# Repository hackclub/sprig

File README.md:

# 🍃 Hack Club Sprig 🍃🍃🍃

**[💻 Online Editor: Make a game](https://sprig.hackclub.com/editor)** | **[👀 Gallery: Find games](https://sprig.hackclub.com/gallery)** | **[🕸 Landing Page](https://sprig.hackclub.com)** | **[🎮 Firmware](https://github.com/hackclub/sprig/tree/main/firmware/spade)** | **[👾 Engine](https://github.com/hackclub/sprig-engine)**

[Sprig](https://sprig.hackclub.com) is a game console where **every user is a creator**. It can only be obtained by building a tile-based game in the [web-based game editor](https://sprig.hackclub.com/editor) and shipping it in the [community gallery](https://sprig.hackclub.com/gallery). It's made by [Hack Club](https://hackclub.com).

<p align="left">

</p>

You should be able to get started in Sprig with very little programming experience. Even if you're an expert, you should still be able to have fun. Sprig games are designed to be shared and hacked on with friends. Every game submitted is easily viewable and editable in our gallery allowing people to learn from and build off each other. 

## Sprig is a...

...**custom handheld game console** built by Hack Club. we are giving a Sprig to every teenage hacker that successfully shares a game they create in our [community gallery](https://sprig.hackclub.com/gallery).

<p align="left">

</p>

...**[web-based game editor](https://sprig.hackclub.com/editor)** that transforms learning to code from studying language syntax to making small creative projects. The Sprig game engine exposes a small construction kit for making tile-based games. This construction kit helps you focus on being creative instead of learning big APIs. The games are just JavaScript and we built a custom system to run that same JavaScript on the microcontroller!

<p align="left">

</p>

...**[hardware development kit](https://github.com/hackclub/sprig/blob/main/docs/ASSEMBLY.md)**. It's not just for gaming! The Sprig console is designed to be assembled and disassembled. Each kit includes parts needed for getting started with hardware engineering and embedded systems programming. This includes a Raspberry Pi Pico, a TFT7735 screen, a MAX98357A I2S class D audio amplifier, a whole bunch of buttons, LEDs, a speaker, and a carrier board which wires all these components together while exposing the remaining pins on the microcontroller. It's a complete system for generating graphics, sound, and handling tactile inputs which is reprogrammable at the touch of a button.

<p align="left">

</p>

## Fully open source

**Sprig is open source**. Shipping a game to the Sprig Gallery is contributing to an open-source project. Everything about Sprig is transparent and editable. That includes the [hardware designs](https://github.com/hackclub/sprig/tree/main/hardware), the [game engine](https://github.com/hackclub/sprig/tree/main/engine), the [embedded game engine for the RP2040 chip](https://github.com/hackclub/sprig/tree/main/firmware/spade), and the editor and website itself in this repo!

We did some fun engineering to get Sprig to work and to make your games run the same on your desktop computer and a $4 microcontroller. That involved custom JS runtimes with optimizations in C and even PIO assembly. We also documented some [behind-the-scenes](https://github.com/hackclub/sprig/tree/main/docs).

## You Ship, We Ship

Make a game
&rarr; Share it with the community
&rarr; Receive your device
&rarr; Play Sprig games on it
&rarr; Hack on the device for more projects

***Only teenagers and younger can receive Sprigs!*** All are welcome to submit to the [gallery](https://sprig.hackclub.com/gallery) though.

## Philosophy

People learn best when they make things that they care about, which they can then share with others. This type of learning philosophy is called constructionism, and Sprig is a type of microworld. A microworld is an environment where you can discover programming by using it to express yourself. 

## Tutorials

To get started you can follow [this challenge in the editor](https://sprig.hackclub.com/gallery/getting_started), check out some [Sprig workshops](https://workshops.hackclub.com#sprig) or [Sprig jams](https://jams.hackclub.com/batch/sprig).

## Development

Join the `#sprig` channel on the [Hack Club Slack](https://hackclub.com/slack/) where you can join the development discussion and ask for help. We also have other channels for Sprig specific stuff:

- `#sprig-platform`: For discussion of development of the Sprig platform as a whole. 
- `#sprig-gaming-controller`: Building a case for the Sprig console to make it a portable gaming controller.
- `#sprig-emulator`: Development of a Gameboy emulator for Sprig.
- `#sprig-multiplayer`: Development of multiplayer support.
- `#sprig-lora`: Development of Sprig-Lora communicator.
- `#sdsprig`: Development of Sprig loading from an SD Card.
- `#sprig-minecraft`: Development of Minecraft for Sprig.
- `#sprig-ios-app`: Development of iOS app.
- `#sprig-engagement`: Development of a bot to post every new game to `#sprig`.
- `#vs-sprig`: Development of Sprig extension for VS Code.
- `#stationary-sprig`: Making Sprig a home console.
- `#spriggy-doom`: Development of a clone of Doom.
- `#sprigos-development`: Development of the sprigOS, the sprig game that acts like an operating system.
- `#spade`: For discussions of Spade firmware/OS of the Sprig.
- `#spaint`: Make art with your sprig with sPaint and share.

Learn more about how to make games with Sprig check out the [docs](https://github.com/hackclub/sprig/tree/main/docs).

### Tech Stack

Sprig's editor and site pages are built with [Astro](https://astro.build/) (SSR via `@astrojs/node`) using [Preact](https://preactjs.com/) for rendering. Perhaps somewhat unusually, we predominantly use [Preact Signals](https://preactjs.com/guide/v10/signals/) for state management. The code editor uses [CodeMirror](https://codemirror.net/). There is one legacy [Svelte](https://svelte.dev/) component on the homepage. The database is [Firebase](https://firebase.google.com/). Everything pushed to GitHub and all pull requests are automatically deployed on [Vercel](https://vercel.com/hackclub).

### Repo Structure

```tree
sprig/
├── src/                        # Astro website + editor
│   ├── pages/                  # Pages (.astro) and API routes (.ts), all SSR
│   ├── components/             # Preact (TSX) UI components + CSS modules
│   ├── lib/                    # Shared support code (server + client)
│   ├── legacy/                 # Old Svelte code kept for the homepage
│   ├── layouts/                # Astro layout templates
│   ├── integrations/           # Custom Astro integrations
│   ├── translations/           # i18n strings
│   ├── global.css              # Global styles
│   └── middleware.ts           # Astro middleware
│
├── engine/                     # Sprig game engine (separate package)
├── games/                      # Community-submitted game files (.js)
├── public/                     # Static assets (game metadata, images, fonts)
├── firmware/                   # RP2040 embedded firmware (Spade runtime + HAL)
├── hardware/                   # PCB designs + 3D-printable console cases
├── docs/                       # Documentation (assembly, getting started, runbooks)
├── scripts/                    # Python admin tools (plagiarism check, review, etc.)
├── bin/                        # lint-sprig game linter
├── tests/                      # Fuzzy tests for the engine
├── yjs-client/                 # Yjs WebRTC client for collaborative editing
├── yjs-signaling-server/       # Yjs signaling server (separate deploy)
├── font-things/                # Font manipulation script
└── sprig-hax/                  # Community hardware mods (gyro, etc.)
```

Key source directories explained:

- `src/pages/` contains all the site's main pages and API routes. In general, `.ts` files are API routes and `.astro` files are pages. All pages are server-side rendered on demand and can make database calls and such.
- `src/components/` contains all the components used in the editor and site pages. Most components will have accompanying `.module.css` files which contain vanilla CSS stylesheets which are scoped to the component. These "CSS modules" can be imported as a JS object containing referencable class names.
- `src/lib/` contains all the support code. Currently this is a mix of server and client code.
- `src/legacy/` has a bunch of old code from the v1 version of the editor which is kept for ease of porting the home and Get a Sprig pages. Since Astro lets us combine multiple frameworks, we're also using old Svelte code in some places.
- `docs/` contains documentation on how to use Sprig, including `docs.md` which contains the help file embedded in the editor.
- `public/` contains static assets which are directly served.
- `src/global.css` and `src/components/standard-head.astro` contain code that's generally shared across all pages.

### Prerequisites

Things you'll want installed:

- [Git](https://git-scm.com/)
- [Bun](https://bun.sh/)

We use Firebase as a database. To develop login/saving related features locally, you'll likely want to [create a Firebase project](https://console.firebase.google.com/) for yourself. Then, create a service account, download the JSON file, and convert the contents to base64 ([link to a tool to easily do this](https://gchq.github.io/CyberChef/#recipe=JSON_Minify()To_Base64('A-Za-z0-9%2B/%3D'))).

We recommend [Visual Studio Code](https://code.visualstudio.com/) as a code editor. You should be automatically prompted to install some recommended extensions when you open the project.

### Project Setup

In a terminal, clone the repo and install packages:

```bash
git clone https://github.com/hackclub/sprig/
cd sprig
bun install
```

Next, you'll want to give Sprig access to the Firebase credentials, as well as some extra credentials that you can request from the @creds team on Slack. Complete the `.env.example` file with those credentials and rename it to `.env`.

To start the dev server, run `bun dev` and visit <http://localhost:4321> in your web browser! Please create a GitHub issue if you cannot get something to work properly.

### Running Tests

```bash
bun test          # fuzzy engine tests
bun run test:unit # vitest unit tests
```

### Docker

```bash
docker compose up
```

This starts the Astro site (port 9996), yjs-client, and yjs-signaling-server.

### Engine Development

All *engine code* (responsible for running games, playing tunes, etc.) is in a different repo: <https://github.com/hackclub/sprig-engine/>.

If you want to work on the engine and test out your changes in the context of this repo, you'll want to use a feature called linking.

First set up the engine repo:

```bash
git clone https://github.com/hackclub/sprig-engine/
cd sprig-engine
bun install
bun link
```

Then, in this website's repo:

```bash
bun link sprig
```

Now, run `bun dev` in the engine repo to start the TypeScript build process.

## Acknowledgements

The Sprig was developed by a team at Hack Club with assistance from Brian Silverman (who helped develop Scratch and the precursor to Lego Mindstorms), Vadim Gerasimov (engineer at Google who helped create Tetris when he was 15), and Quentin Bolsée (researcher at MIT and Vrije University Brussels), and dozens contributions from teenage open-source developers!

We're also grateful for amazing open-source projects that make this possible like [Kaluma](https://kalumajs.org/), [JerryScript](https://jerryscript.net/), [uhtml](https://github.com/WebReflection/uhtml), and [CodeMirror](https://codemirror.net/).

## Responsibilities

Please refer to [this document](./RESPONSIBILITIES.md) for a list of current team members who are accountable for maintaining certain aspects of the Sprig platform.

## License

The Hack Club Sprig is open source and licensed under the [MIT License](./LICENSE). Fork, remix, and make it your own! Pull requests and other contributions greatly appreciated.

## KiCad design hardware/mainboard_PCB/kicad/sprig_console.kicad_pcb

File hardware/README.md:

## The Sprig Console

You can find KiCAD 6 files for the PCB of Sprig, a BOM, and CAD models for the acrylic back covers here.

- `hardware/` contains the KiCAD files and Bill of Materials for the PCB
- `back_covers/` contains the CAD models for the acrylic back covers

The main [Sprig Repo is available here](https://www.github.com/hackclub/sprig).

# Description

The Sprig console is a custom-designed, limited edition game console powered by the Raspberry Pi Pico. It has a 1.8" 160x128 LCD display, as well as eight tactile buttons for input. It uses two AAA batteries for power, and has a MAX98357A audio amplifier with an 8 ohm, 300mW Speaker.

The Sprig console is a custom-designed, limited edition game console built to run games written with the Sprig game editor.

It's powered by a Raspberry Pi RP2040, which is clocked at 125MHz, with 264kB SRAM and 2MB external QSPI flash. Four unused GPIO pins are exposed to the rear of the console.

The Sprig is powered by two AAA batteries. There is also a high efficiency schottky diode to prevent power flow to the batteries when connected to USB power.

In addition, there is a MAX98357A class D audio amplifier from Maxim Integrated, connected to a CUI Devices CVS-1508 8 ohm, 300mW speaker.

There are two LEDs for status, a power switch for batteries, as well as eight tactile buttons to control input.

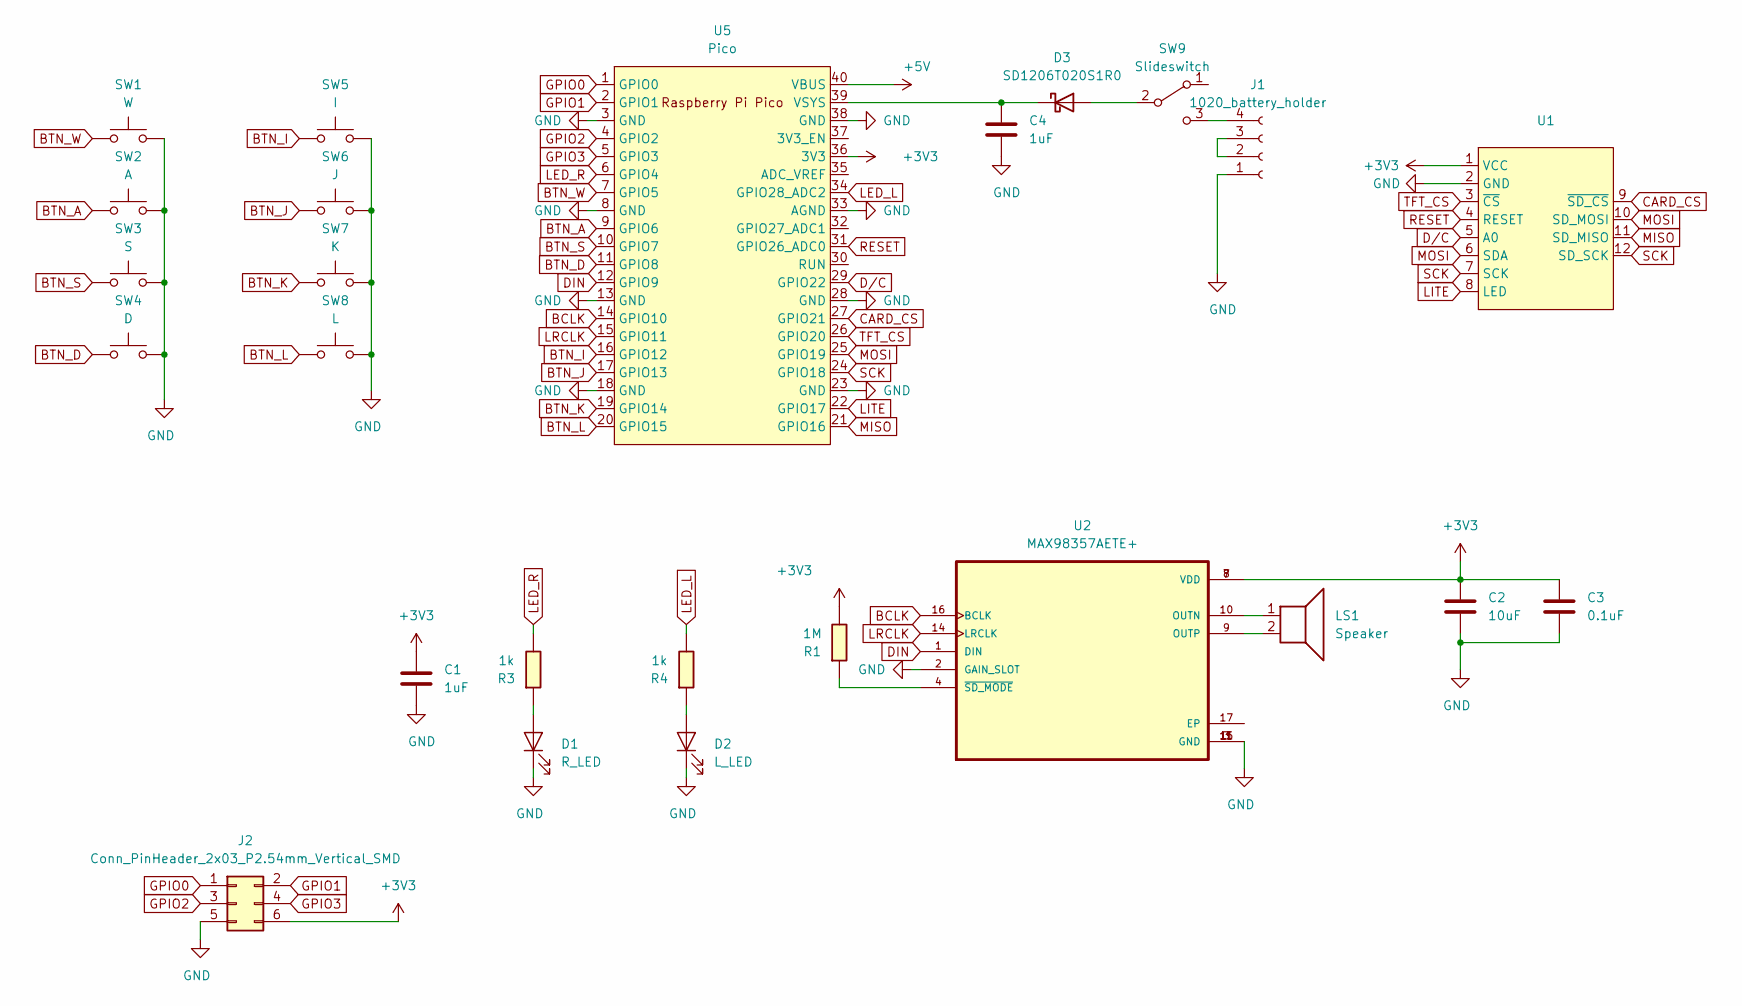
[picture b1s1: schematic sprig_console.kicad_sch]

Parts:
C1, C4: 1uF; C_1206
C2: 10uF; C_1206
C3: 0.1uF; C_1206
D1: R_LED; LED_1206
D2: L_LED; LED_1206
D3: SD1206T020S1R0; Diode_Schotky_100V_1A_Mini_SMA
J1: 1020_battery_holder; 1022
J2: Conn_PinHeader_2x03_P2.54mm_Vertical_SMD; PinHeader_2x03_P2.54mm_Vertical_SMD
LS1: Speaker; CVS-1508
R1: 1M; R_1206
R3, R4: 1k; R_1206
SW1: W; SW_PUSH-12mm_Wuerth-430476085716
SW2: A; SW_PUSH-12mm_Wuerth-430476085716
SW3: S; SW_PUSH-12mm_Wuerth-430476085716
SW4: D; SW_PUSH-12mm_Wuerth-430476085716
SW5: I; SW_PUSH-12mm_Wuerth-430476085716
SW6: J; SW_PUSH-12mm_Wuerth-430476085716
SW7: K; SW_PUSH-12mm_Wuerth-430476085716
SW8: L; SW_PUSH-12mm_Wuerth-430476085716
SW9: Slideswitch; slideswitchCK
U1: TFT_MSP1803
U2: MAX98357AETE+; QFN50P300X300X80-17N
U5: Pico; RPi_Pico_SMD_TH_mod

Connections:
+3V3: C1.1, C2.1, C3.1, J2.6, R1.1, U1.1 (VCC), U2.7 (VDD), U2.8 (VDD), U5.36 (3V3)
+5V: U5.40 (VBUS)
BCLK: U2.16 (BCLK), U5.14 (GPIO10)
BTN_A: SW2.1, U5.9 (GPIO6)
BTN_D: SW4.1, U5.11 (GPIO8)
BTN_I: SW5.1, U5.16 (GPIO12)
BTN_J: SW6.1, U5.17 (GPIO13)
BTN_K: SW7.1, U5.19 (GPIO14)
BTN_L: SW8.1, U5.20 (GPIO15)
BTN_S: SW3.1, U5.10 (GPIO7)
BTN_W: SW1.1, U5.7 (GPIO5)
CARD_CS: U1.9 (~SD_CS), U5.27 (GPIO21)
DIN: U2.1 (DIN), U5.12 (GPIO9)
D/C: U1.5 (A0), U5.29 (GPIO22)
GND: C1.2, C2.2, C3.2, C4.2, D1.1 (K), D2.1 (K), J1.1, J2.5, SW1.2, SW2.2, SW3.2, SW4.2, SW5.2, SW6.2, SW7.2, SW8.2, U1.2 (GND), U2.2 (GAIN_SLOT), U2.3 (GND), U2.11 (GND), U2.15 (GND), U5.3 (GND), U5.8 (GND), U5.13 (GND), U5.18 (GND), U5.23 (GND), U5.28 (GND), U5.33 (AGND), U5.38 (GND)
GPIO0: J2.1, U5.1 (GPIO0)
GPIO1: J2.2, U5.2 (GPIO1)
GPIO2: J2.3, U5.4 (GPIO2)
GPIO3: J2.4, U5.5 (GPIO3)
LED_L: R4.1, U5.34 (GPIO28_ADC2)
LED_R: R3.1, U5.6 (GPIO4)
LITE: U1.8 (LED), U5.22 (GPIO17)
LRCLK: U2.14 (LRCLK), U5.15 (GPIO11)
MISO: U1.11 (SD_MISO), U5.21 (GPIO16)
MOSI: U1.6 (SDA), U1.10 (SD_MOSI), U5.25 (GPIO19)
unnamed: D1.2 (A), R3.2
unnamed: D2.2 (A), R4.2
unnamed: D3.2 (A), SW9.2 (B)
unnamed: C4.1, D3.1 (K), U5.39 (VSYS)
unnamed: J1.2, J1.3
unnamed: J1.4, SW9.3 (C)
unnamed: LS1.1, U2.10 (OUTN)
unnamed: LS1.2, U2.9 (OUTP)
unnamed: R1.2, U2.4 (~SD_MODE)
RESET: U1.4 (RESET), U5.31 (GPIO26_ADC0)
SCK: U1.7 (SCK), U1.12 (SD_SCK), U5.24 (GPIO18)
TFT_CS: U1.3 (~CS), U5.26 (GPIO20)

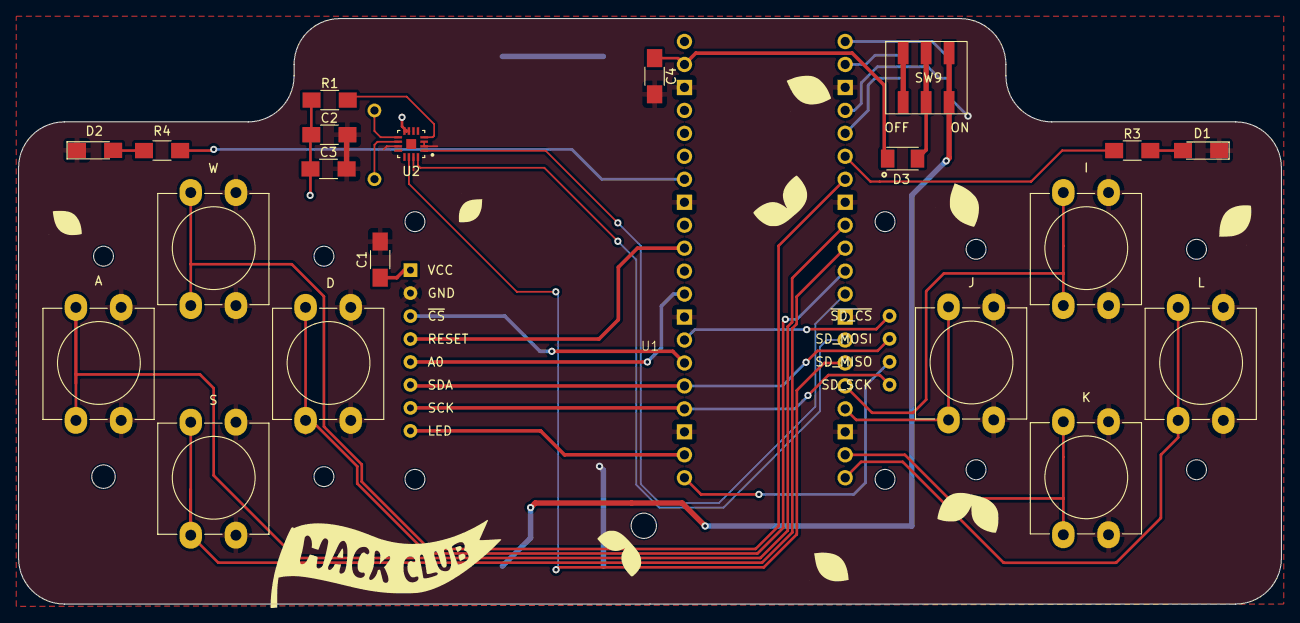
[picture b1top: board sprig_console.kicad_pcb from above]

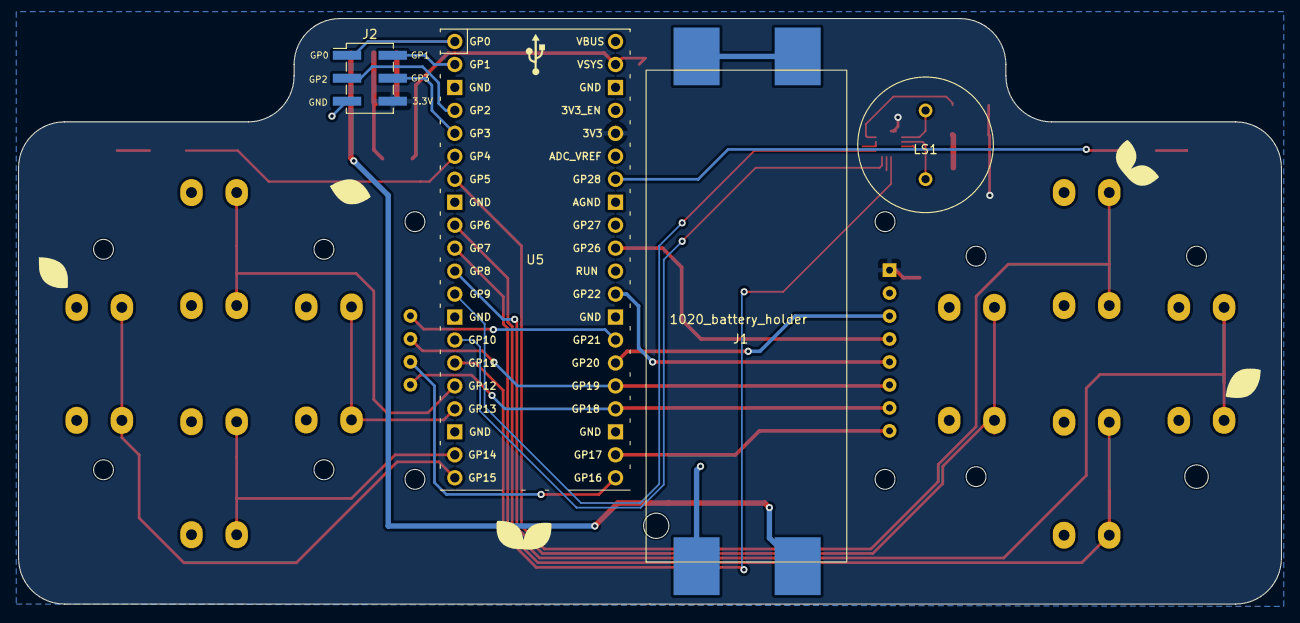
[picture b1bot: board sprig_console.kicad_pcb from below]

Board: 2 copper layers, 139.7 x 64.8 mm, 26 parts (5 on the bottom side), 36 nets.

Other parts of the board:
Ref**: Val**; usb

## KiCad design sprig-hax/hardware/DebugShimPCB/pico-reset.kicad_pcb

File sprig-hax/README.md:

# SPRIGHAX

Hacking the sprig with experimental hardware and software features.

Sprighax #1. Custom board, UART, & Gyro 

*none of my fellows be hacking the sprig. it's time to start sprigmaxxing*

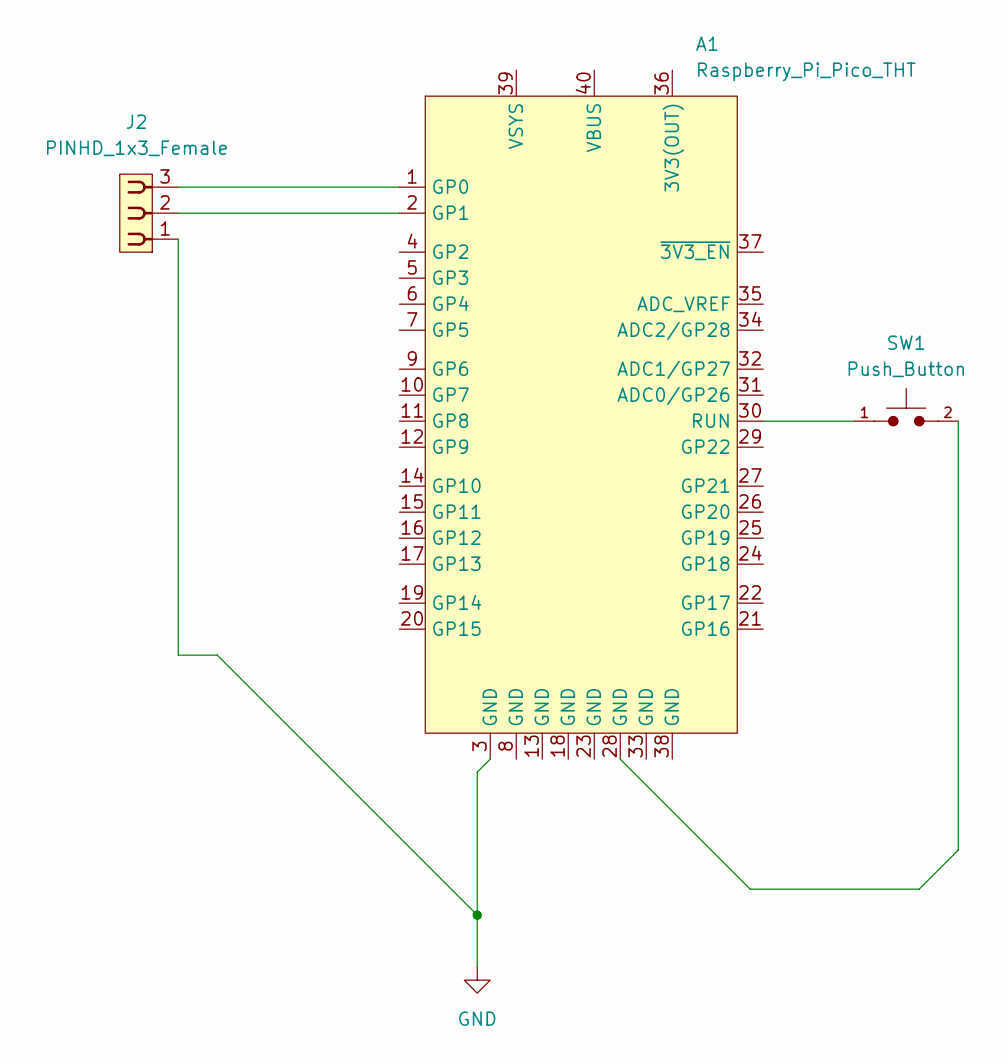
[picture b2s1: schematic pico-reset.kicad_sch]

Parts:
A1: Raspberry_Pi_Pico_THT; raspberry_pi_pico_THT
J2: PINHD_1x3_Female; PinSocket_1x03_P2.54mm_Vertical
SW1: Push_Button; SW_SPST_B3U-3100P

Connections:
GND: A1.3 (GND), J2.1
unnamed: A1.28 (GND), SW1.2
unnamed: A1.1 (GP0), J2.3
unnamed: A1.2 (GP1), J2.2
unnamed: A1.30 (RUN), SW1.1

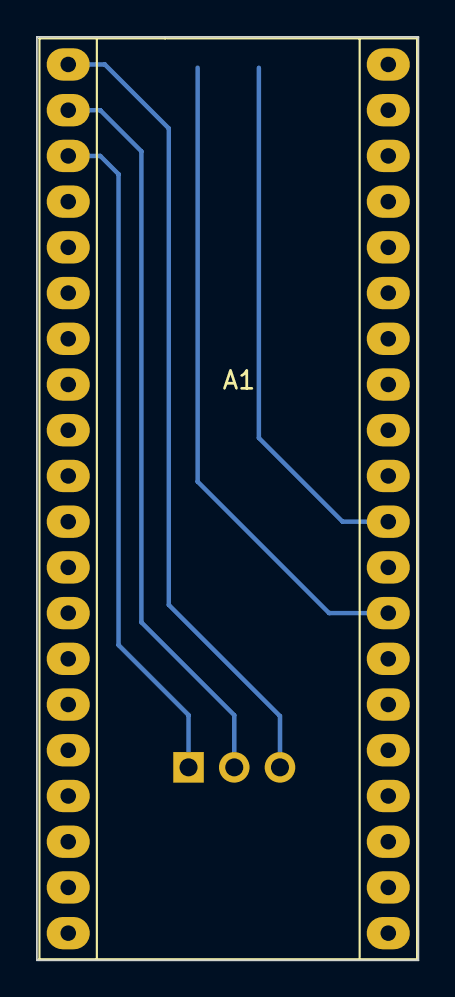
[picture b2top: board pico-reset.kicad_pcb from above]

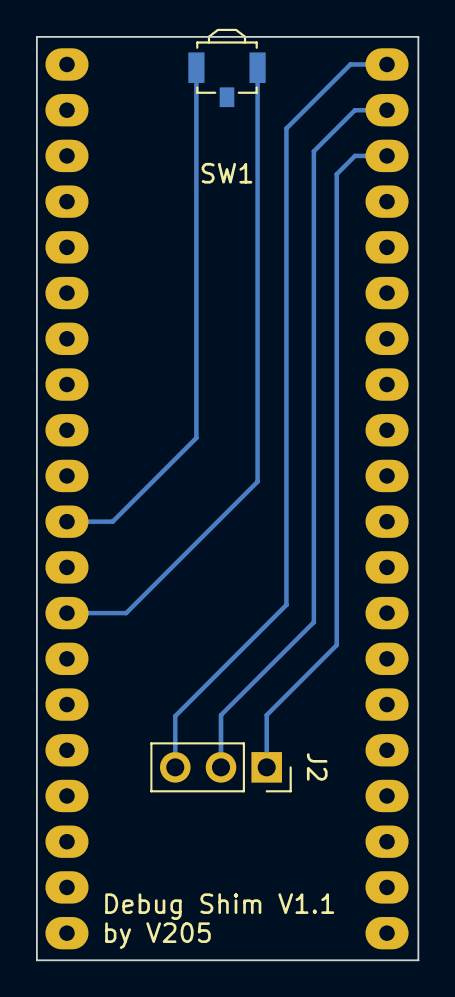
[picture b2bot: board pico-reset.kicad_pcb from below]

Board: 2 copper layers, 21.2 x 51.3 mm, 3 parts (2 on the bottom side), 5 nets.
